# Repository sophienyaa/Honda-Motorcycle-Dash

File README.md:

# Honda Motorcycle Dash

**NOTE: This is a 'Alpha' and a work in progress**

## What is this?

This is my attempt to build an information display / dashboard replacement (or additon) for modern Honda motorcycles. It connects to the bike via its diagnostic port and reads information directly from the ECU

It also contains a GPS module and support for an ambient temperature / humidity sensor

## Hardware

The below hardware is used in the current design. For further information see the [hardware](https://github.com/mickwheelz/Honda-Motorcycle-Dash/wiki/Hardware) section of the wiki

* Espressif ESP32 (Node32S for development, ESP32WROOM for build)
* 2.8" ILI9341 based SPI TFT Display
* DHT22 Temperature/Humidity Sensor
* Serial GPS Module
* L9637D Monolithic bus driver with ISO 9141 interface

Eagle CAD files for the hardware are available in the `pcb` folder, and designs for 3D printing a housing are available in the `case` folder

## Software & Features

The code is written for the ESP32 in C\C++ and is designed to be built with PlatformIO

On startup the device connects to the bike's ECU and displays the following information

* Engine Temperature
* Engine RPM
* Battery Voltage
* Throttle Position %
* Intake Air Temperature C
* Neutral Switch
* Side Stand Switch
* Bike Speed

It also displays the following information from other sensors

* GPS Speed (GPS)
* Ambient Temperature (DHT22)

The below features are intended to be available in the future

* Gear Position (Based on Speed + RPM) (ECU)
* Heading (North, South, East, West, etc) (GPS)
* Ambient Humidity (DHT22)
* Smartphone Notifications (ESP32 BLE)
* Smartphone "Now Playing" (ESP32 BLE)

For further information, see the [software](https://github.com/mickwheelz/Honda-Motorcycle-Dash/wiki/Software) section of the wiki section of the wiki

## Special Thanks To

This project would not be possible without the below information and open source code

Working with Honda ECU's
* Aster94's KWP2000 Library - https://github.com/aster94/Keyword-Protocol-2000
* Gonzo's CTX-OBD Project - https://gonzos.net/projects/ctx-obd/
* PGMFI Formus - http://forum.pgmfi.org/

Arduino Libraries and Tools
* Adafruit's GFX/DHT/ILI9341/BusIO Libraries - https://learn.adafruit.com/adafruit-gfx-graphics-library/overview
* Mikalhart's TinyGPS++ - https://github.com/mikalhart/TinyGPSPlus
* Javl's image2cpp - https://javl.github.io/image2cpp/
* Ropg's truetype2gfx - https://rop.nl/truetype2gfx/

## Disclaimer

This code is provided under the GNU GPLv3 and includes NO WARRANTY.

The authors accept NO LIABILITY for damages or destruction to any property or persons through the use of this software or hardware design.

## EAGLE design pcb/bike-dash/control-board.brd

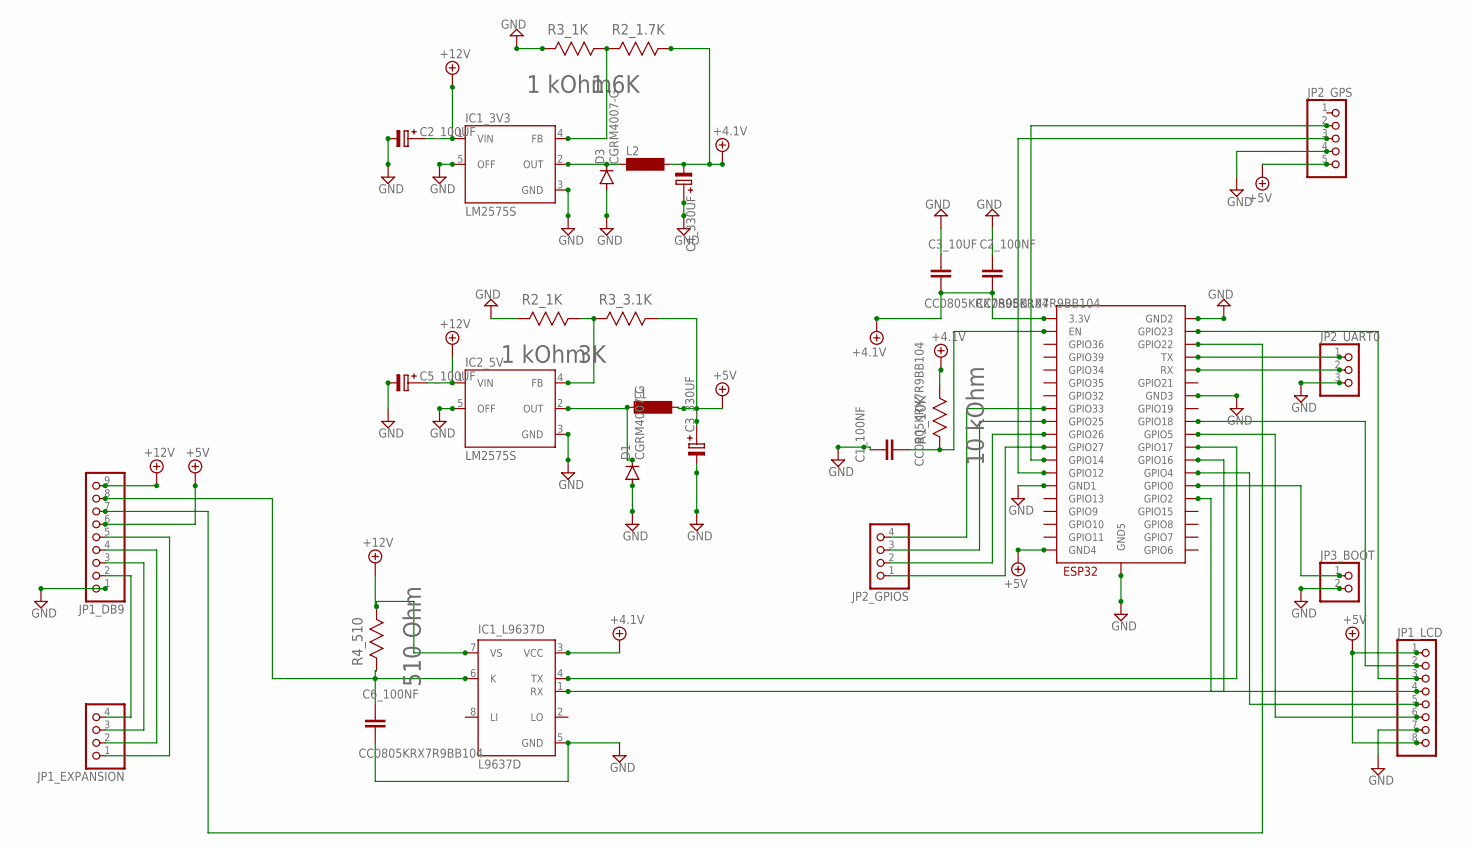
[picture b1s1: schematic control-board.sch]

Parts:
C1_100NF, C2_100NF, C3_10UF, C6_100NF: CC0805KRX7R9BB104; CAP_0805
C2_100UF, C5_100UF: C-PR-SMD-SV-E/F; SV-E/F
C3_330UF, C4_330UF: C-PR-SMD-SV-D; SV-D
D1, D3: CGRM4007-G; SOD-123_MINI-SMA
ESP32: ESP32-WROOM
IC1_3V3, IC2_5V: LM2575S; TO263-5
IC1_L9637D: L9637D; SO08
JP1_DB9: PINHD-1X9/90; 1X09/90
JP1_EXPANSION, JP2_GPIOS: PINHD-1X4/90; 1X04/90
JP1_LCD: PINHD-1X8; 1X08
JP2_GPS: PINHD-1X5; 1X05
JP2_UART0: PINHD-1X3/90; 1X03/90
JP3_BOOT: PINHD-1X2/90; 1X02/90
L1, L2: MS85
R1_10K: 10 kOhm; RESC2013X65N
R2_1.7K: 1.6K; RESC2013X65N
R2_1K, R3_1K: 1 kOhm; RESC2013X65N
R3_3.1K: 3K; RESC2013X65N
R4_510: 510 Ohm; RESC2013X65N

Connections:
+4.1V: C2_100NF.2, C3_10UF.2, C4_330UF.-, ESP32.3V3 (3.3V), IC1_L9637D.3 (VCC), L2.2, R1_10K.1 (R1), R2_1.7K.1 (R1)
+5V: C3_330UF.+, ESP32.GND4, JP1_DB9.6, JP1_LCD.1, JP1_LCD.8, JP2_GPS.5, L1.2, R3_3.1K.1 (R1)
+12V: C2_100UF.+, C5_100UF.+, IC1_3V3.1 (VIN), IC1_L9637D.7 (VS), IC2_5V.1 (VIN), JP1_DB9.9, R4_510.1 (R1)
GND: C1_100NF.1, C2_100NF.1, C2_100UF.-, C3_10UF.1, C3_330UF.-, C4_330UF.+, C5_100UF.-, C6_100NF.2, D1.A, D3.A, ESP32.GND1, ESP32.GND2, ESP32.GND3, ESP32.GND5, IC1_3V3.3 (GND), IC1_3V3.5 (OFF), IC1_L9637D.5 (GND), IC2_5V.3 (GND), IC2_5V.5 (OFF), JP1_DB9.1, JP1_LCD.7, JP2_GPS.4, JP2_UART0.3, JP3_BOOT.2, R2_1K.2 (R2), R3_1K.2 (R2)
unnamed: C1_100NF.2, ESP32.EN, R1_10K.2 (R2)
unnamed: D3.C, IC1_3V3.2 (OUT), L2.1
unnamed: C6_100NF.1, IC1_L9637D.6 (K), JP1_DB9.8, R4_510.2 (R2)
unnamed: D1.C, IC2_5V.2 (OUT), L1.1
unnamed: IC1_3V3.4 (FB), R2_1.7K.2 (R2), R3_1K.1 (R1)
unnamed: ESP32.IO0 (GPIO0), JP3_BOOT.1
unnamed: ESP32.TX, JP2_UART0.1
unnamed: ESP32.RX, JP2_UART0.2
unnamed: IC2_5V.4 (FB), R2_1K.1 (R1), R3_3.1K.2 (R2)
unnamed: ESP32.IO22 (GPIO22), JP1_DB9.7
unnamed: JP1_DB9.2, JP1_EXPANSION.4
unnamed: ESP32.IO17 (GPIO17), IC1_L9637D.4 (TX)
unnamed: ESP32.IO16 (GPIO16), IC1_L9637D.1 (RX)
unnamed: ESP32.IO12 (GPIO12), JP2_GPS.3
unnamed: ESP32.IO14 (GPIO14), JP2_GPS.2
unnamed: JP1_DB9.3, JP1_EXPANSION.3
unnamed: JP1_DB9.4, JP1_EXPANSION.2
unnamed: JP1_DB9.5, JP1_EXPANSION.1
unnamed: ESP32.IO5 (GPIO5), JP1_LCD.6
unnamed: ESP32.IO4 (GPIO4), JP1_LCD.5
unnamed: ESP32.IO2 (GPIO2), JP1_LCD.4
unnamed: ESP32.IO23 (GPIO23), JP1_LCD.3
unnamed: ESP32.IO18 (GPIO18), JP1_LCD.2
unnamed: ESP32.IO27 (GPIO27), JP2_GPIOS.1
unnamed: ESP32.IO26 (GPIO26), JP2_GPIOS.2
unnamed: ESP32.IO25 (GPIO25), JP2_GPIOS.3
unnamed: ESP32.IO33 (GPIO33), JP2_GPIOS.4

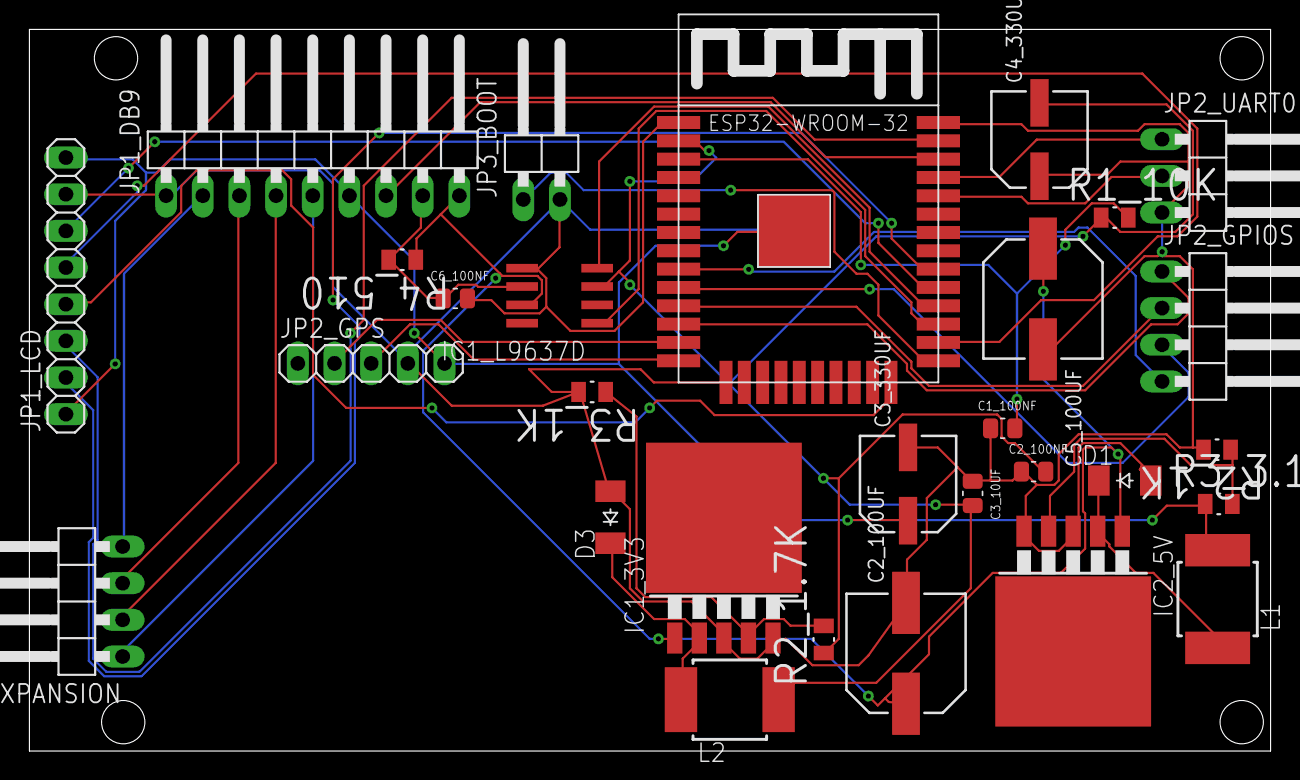
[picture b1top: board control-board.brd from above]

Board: 2 copper layers, 86.0 x 50.0 mm, 29 parts (0 on the bottom side), 31 nets.

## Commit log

2020-09-12 add empty readme
2020-09-12 add eagle cad files for PCB
2020-09-12 tidyup, move gfx to seperate file
2020-09-12 added icon gfx, started work on icon support
2020-09-12 add more icons
2020-09-13 more icon support
2020-09-13 significant refactor, moved to files
2020-09-13 even more refactoring
2020-09-13 readme updates
2020-09-13 Create LICENSE
2020-09-14 rename, test with actual bike
2020-09-14 changes to pcb
2020-09-16 more gps and graphic changes
2020-09-17 screen rotation fix
2020-09-18 changes after test run, kph to mph, tps correction
2020-09-18 change to show kph and mph at the same time
2020-09-19 add images for wiki
2020-09-19 Add .circleci/config.yml
2020-09-19 add build scripts
2020-09-19 update circle config
2020-09-19 change image
2020-09-19 use python img
2020-09-19 run build!
2020-09-19 add case 3d files
2020-09-19 add 3d images for wiki
2020-09-19 fixes for gps and dht

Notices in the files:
parts and their libraries:
cap-pan40: Copyright (C) 2004, Bob Starr
